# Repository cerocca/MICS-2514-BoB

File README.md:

# MICS-2614-BoB
MICS-2614 Ozone sensor Breakout Board

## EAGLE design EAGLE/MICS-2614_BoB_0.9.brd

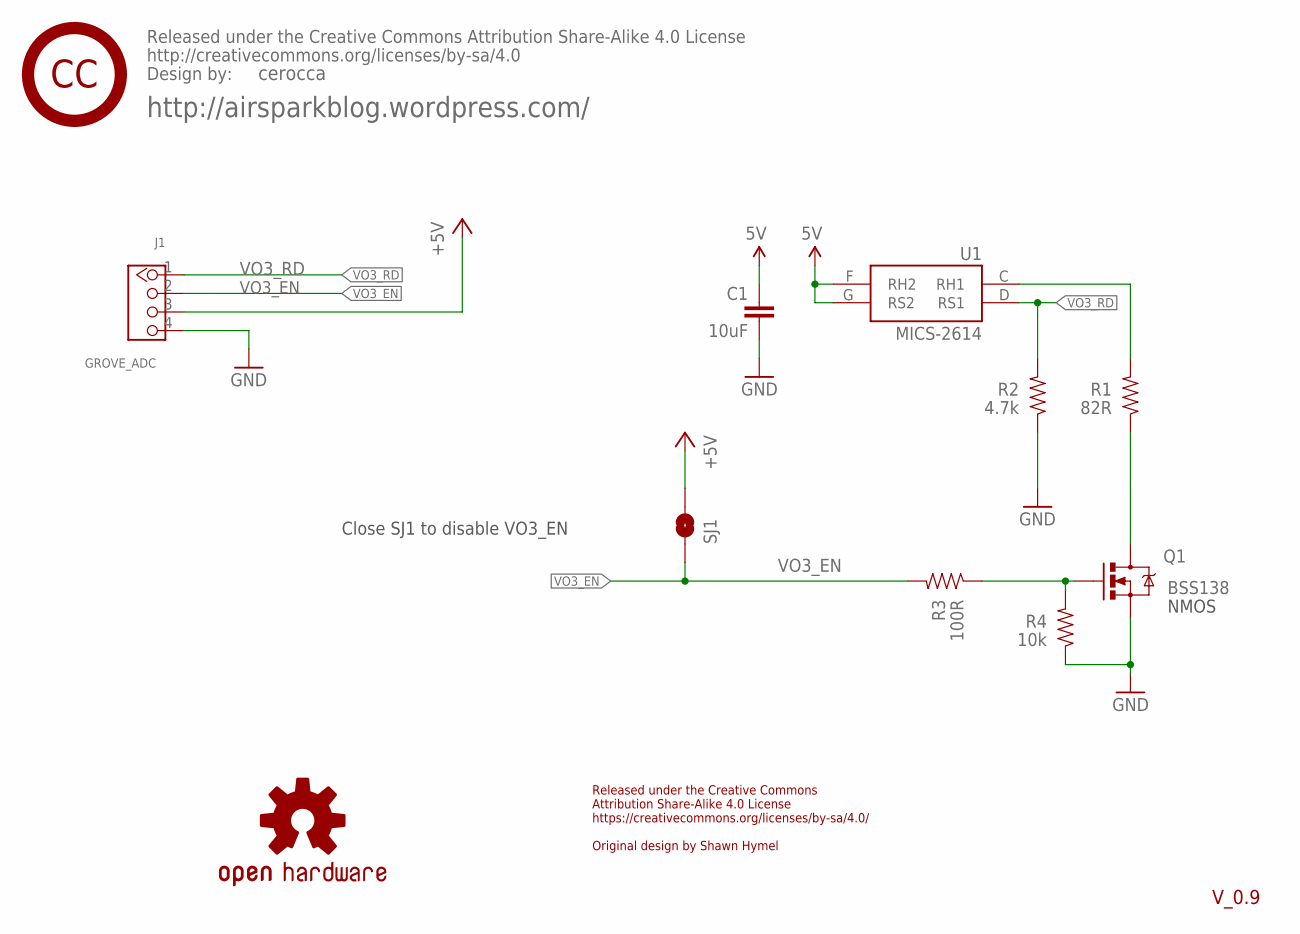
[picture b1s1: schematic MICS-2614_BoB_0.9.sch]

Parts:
C1: 10uF; 0805
J1: GROVE_ADC; 4P-2.0
LOGO2: OSHW-LOGOM; OSHW-LOGO-M
Q1: BSS138; SOT23-3
R1: 82R; 0805
R2: 4.7k; 0805
R3: 100R; 0805
R4: 10k; 0805
SJ1: SOLDERJUMPERNO; SJ_2S-NO
U1: MICS-2614; MICS_10-SMD
U$7: CREATIVE_COMMONS
U$8: CC

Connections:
+5V: C1.1, J1.3, SJ1.2, U1.F (RH2), U1.G (RS2)
GND: C1.2, J1.4, Q1.2 (S), R2.1, R4.1
unnamed: R1.2, U1.C (RH1)
unnamed: Q1.3 (D), R1.1
unnamed: Q1.1 (G), R3.1, R4.2
VO3_EN: J1.2, R3.2, SJ1.1
VO3_RD: J1.1, R2.2, U1.D (RS1)

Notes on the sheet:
V_0.9
Released under the Creative Commons Attribution Share-Alike 4.0 License https://creativecommons.org/licenses/by-sa/4.0/ Original design by Shawn Hymel
http://airsparkblog.wordpress.com/
cerocca
Close SJ1 to disable VO3_EN
NMOS

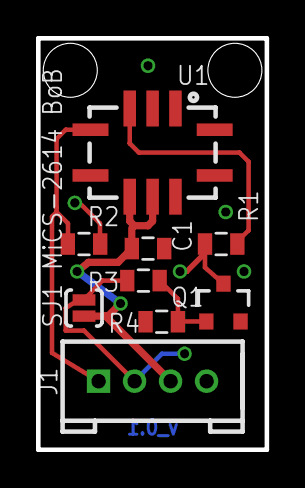
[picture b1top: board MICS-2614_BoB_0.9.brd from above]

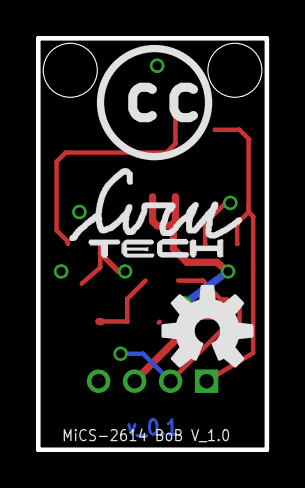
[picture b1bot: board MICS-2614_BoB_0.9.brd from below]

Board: 2 copper layers, 12.7 x 22.9 mm, 13 parts (3 on the bottom side), 7 nets.

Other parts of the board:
U$1: CIRU_1X05

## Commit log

2015-04-03 Update README.md
    corrected sensor name :)
2015-04-03 First Commit
    First (main) commit with:
    - EAGLE files (schematic and layout)
    - Gerber Files (for Seeedstudio Fusion service)
    - BOM in excel format

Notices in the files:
parts and their libraries:
SparkFun-Sensors: Licensing: Creative Commons ShareAlike 4.0 International - https://creativecommons.org/licenses/by-sa/4.0
SparkFun: Licensing: CC v3.0 Share-Alike You are welcome to use this library for commercial purposes.
SparkFun: http://creativecommons.org/licenses/by-sa/4.0
